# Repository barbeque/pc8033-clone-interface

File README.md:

# PC-8033 Clone Interface
This open-source hardware allows original-model NEC PC-8001 computers to use intelligent-type floppy drives such as the PC-8031-2W and PC-80S31.

## BOM
Please consult the [interactive bom](/bom/) for the most helpful view.

| Reference | Component | Digi-Key link | Comment |
|------|-----------|---------------|---------|
| C1 | 220µF capacitor | | |
| C2 | 0.1µF capacitor | | |
| R1 | 4.7kΩ resistor | | |
| U1 | 2x25-pin (50-pin) pin header | | |
| U2 | DIP 74LS32 | | |
| U3 | DIP 74LS04 | | |
| U4 | DIP Intel (or clone) 8255 | | |
| U5 | DIP 74LS30 | | |
| RN1, RN2, RN3 | 4.7kΩ bussed 8-resistor network (9-pin) | | |
| J2 | 2x17 (PC-8031) or 2x18 (PC-80S31) pin header | | |

## Cable from PC-8001
A 50-pin female edge connector and 50-pin female 0.1" IDC header are required. Crimp a straight 50-pin ribbon cable, such that pin 1 of the edge connector connects to pin 1 of the female IDC header. Attach to PC-8033 clone board, paying attention to board callout for pin "01."

## Cable to Floppy Drive
A cable will have to be made to connect to the disk drive.

### PC-8031-2W (34-pin edge connector)
Use an IDC crimper to crimp a 34-pin ribbon into 34-pin female (0.1") and 34-pin edge connector. Do not cross over (pin 1 on J2 should be pin 1 on the floppy drive.)

Connect to floppy drive, paying attention to pin 1 arrow on back.

### PC-80S31 (36-pin 57-series Centronics)
Use an IDC crimper to crimp a 36-pin ribbon into a 36-pin female (0.1") and 36-pin Centronics connector. Do not cross over.

Connect to floppy drive.

## Enclosure
TBD

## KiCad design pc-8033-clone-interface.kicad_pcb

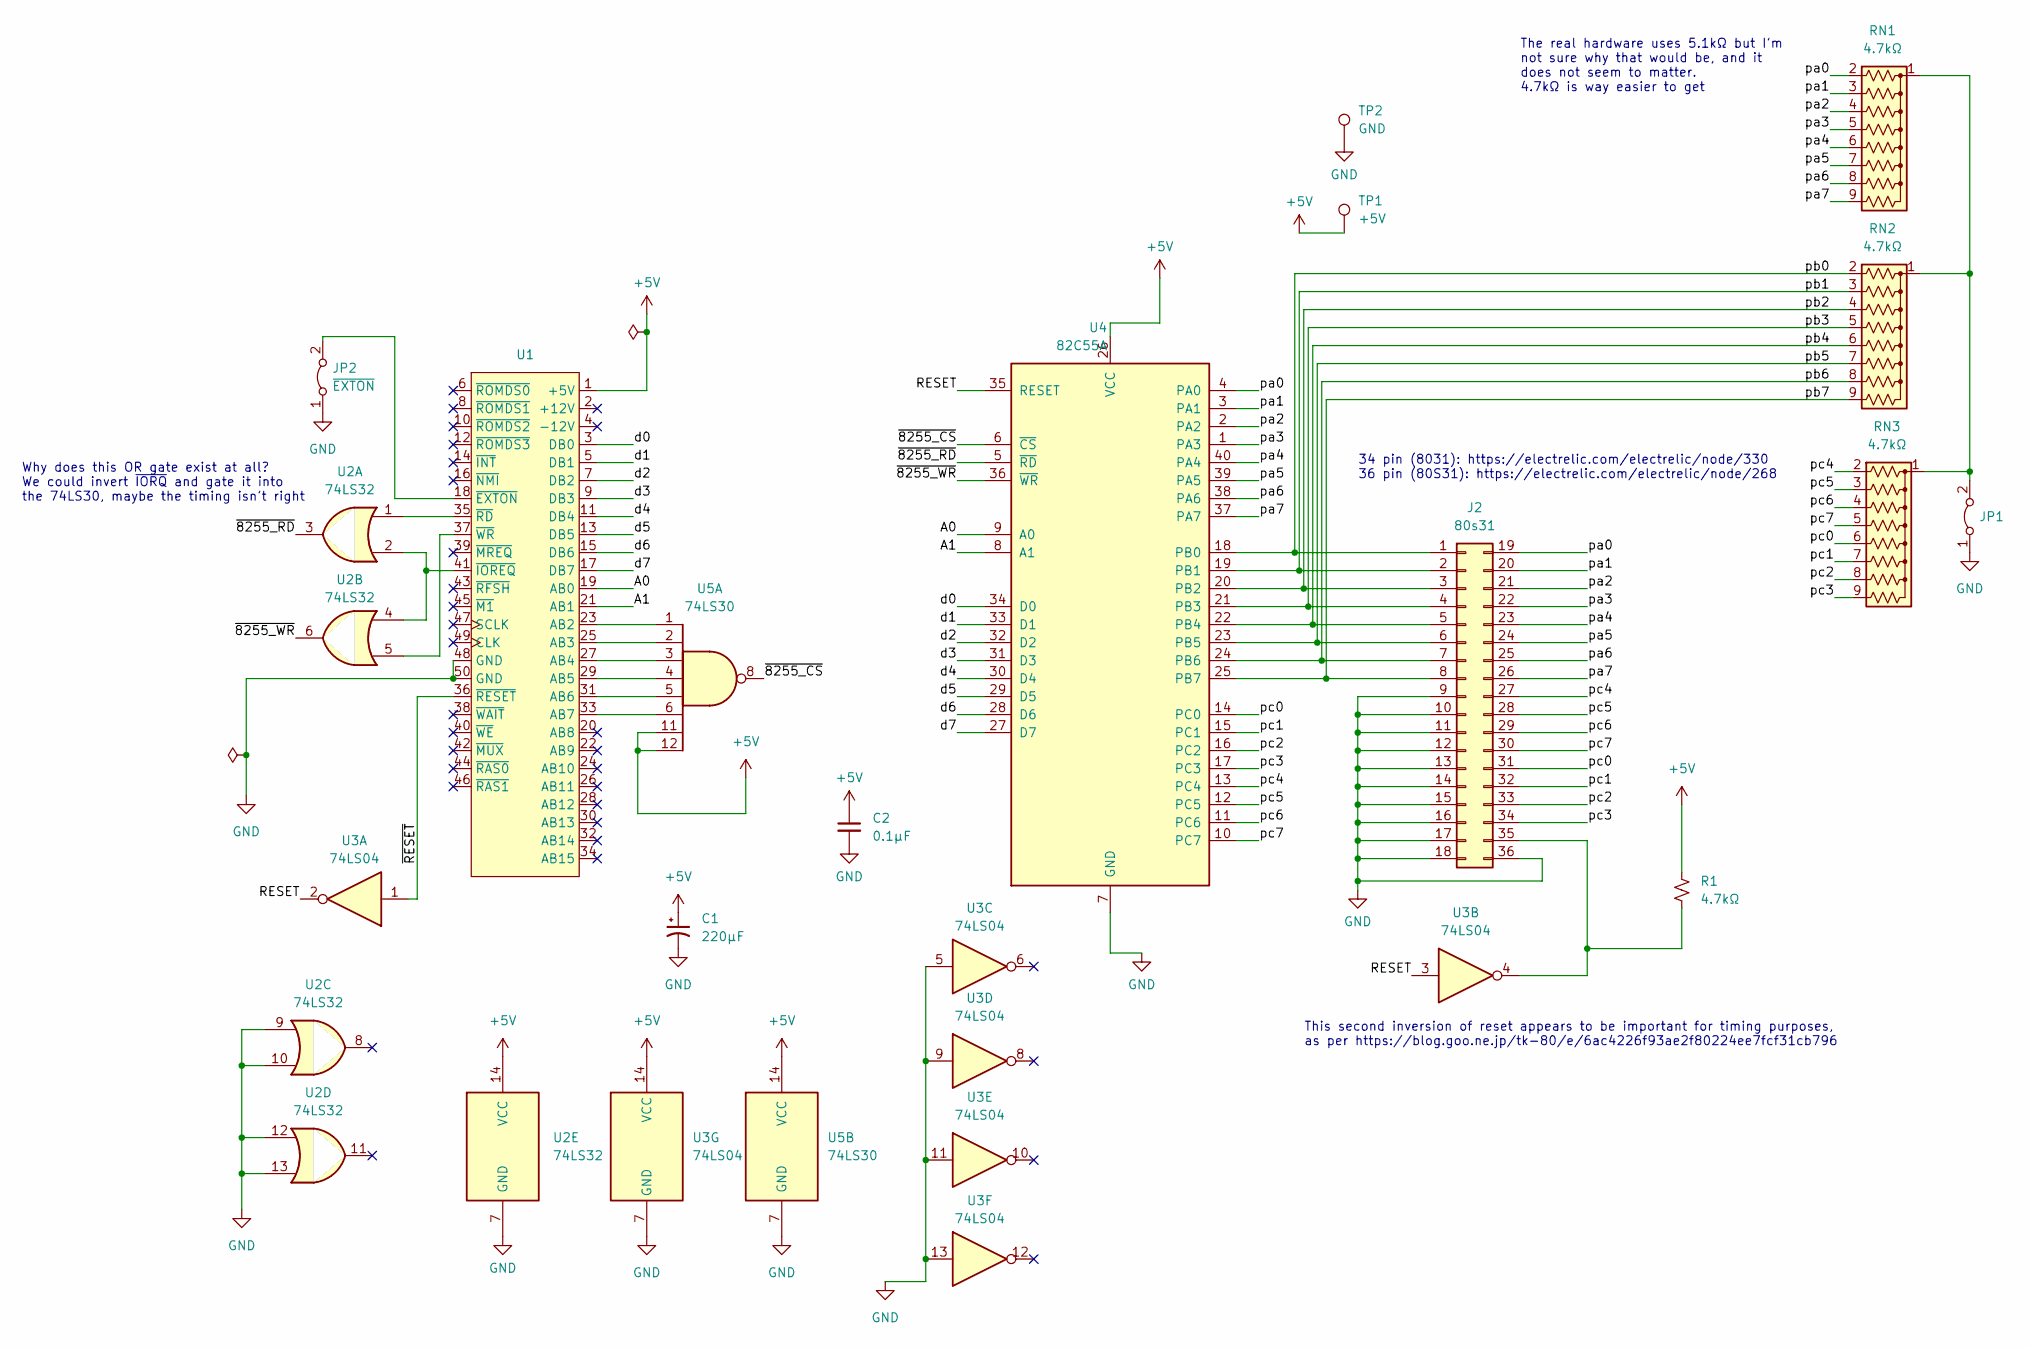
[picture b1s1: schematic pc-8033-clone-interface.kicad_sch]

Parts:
C1: 220µF; CP_Radial_D6.3mm_P2.50mm
C2: 0.1µF; C_Disc_D3.4mm_W2.1mm_P2.50mm
J2: 80s31; Centronics_36_FDD
JP1: Jumper_2_Bridged; SolderJumper-2_P1.3mm_Bridged2Bar_Pad1.0x1.5mm
JP2: ~{EXTON}; SolderJumper-2_P1.3mm_Bridged2Bar_Pad1.0x1.5mm
R1: 4.7kΩ; R_Axial_DIN0309_L9.0mm_D3.2mm_P12.70mm_Horizontal
RN1, RN2, RN3: 4.7kΩ; R_Array_SIP9
TP1: +5V; TestPoint_Loop_D1.80mm_Drill1.0mm_Beaded
TP2: GND; TestPoint_Loop_D1.80mm_Drill1.0mm_Beaded
U1: PinHeader_2x25_P2.54mm_Vertical
U2: 74LS32
U3: 74LS04
U4: 82C55A; DIP-40_W15.24mm
U5: 74LS30; DIP-14_W7.62mm_Socket_LongPads

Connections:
+5V: C1.1, C2.1, R1.1, TP1.1, U1.1 (+5V), U2.14 (VCC), U3.14 (VCC), U4.26 (VCC), U5.11, U5.12, U5.14 (VCC)
/A0: U1.19 (AB0), U4.9 (A0)
/A1: U1.21 (AB1), U4.8 (A1)
/RESET: U3.2, U3.3, U4.35 (RESET)
/d0: U1.3 (DB0), U4.34 (D0)
/d1: U1.5 (DB1), U4.33 (D1)
/d2: U1.7 (DB2), U4.32 (D2)
/d3: U1.9 (DB3), U4.31 (D3)
/d4: U1.11 (DB4), U4.30 (D4)
/d5: U1.13 (DB5), U4.29 (D5)
/d6: U1.15 (DB6), U4.28 (D6)
/d7: U1.17 (DB7), U4.27 (D7)
/pa0: J2.19, RN1.2 (R1), U4.4 (PA0)
/pa1: J2.20, RN1.3 (R2), U4.3 (PA1)
/pa2: J2.21, RN1.4 (R3), U4.2 (PA2)
/pa3: J2.22, RN1.5 (R4), U4.1 (PA3)
/pa4: J2.23, RN1.6 (R5), U4.40 (PA4)
/pa5: J2.24, RN1.7 (R6), U4.39 (PA5)
/pa6: J2.25, RN1.8 (R7), U4.38 (PA6)
/pa7: J2.26, RN1.9 (R8), U4.37 (PA7)
/pb0: J2.1, RN2.2 (R1), U4.18 (PB0)
/pb1: J2.2, RN2.3 (R2), U4.19 (PB1)
/pb2: J2.3, RN2.4 (R3), U4.20 (PB2)
/pb3: J2.4, RN2.5 (R4), U4.21 (PB3)
/pb4: J2.5, RN2.6 (R5), U4.22 (PB4)
/pb5: J2.6, RN2.7 (R6), U4.23 (PB5)
/pb6: J2.7, RN2.8 (R7), U4.24 (PB6)
/pb7: J2.8, RN2.9 (R8), U4.25 (PB7)
/pc0: J2.31, RN3.6 (R5), U4.14 (PC0)
/pc1: J2.32, RN3.7 (R6), U4.15 (PC1)
/pc2: J2.33, RN3.8 (R7), U4.16 (PC2)
/pc3: J2.34, RN3.9 (R8), U4.17 (PC3)
/pc4: J2.27, RN3.2 (R1), U4.13 (PC4)
/pc5: J2.28, RN3.3 (R2), U4.12 (PC5)
/pc6: J2.29, RN3.4 (R3), U4.11 (PC6)
/pc7: J2.30, RN3.5 (R4), U4.10 (PC7)
/~8255_CS: U4.6 (~CS), U5.8
/~8255_RD: U2.3, U4.5 (~RD)
/~8255_WR: U2.6, U4.36 (~WR)
/~RESET: U1.36 (~RESET), U3.1
GND: C1.2, C2.2, J2.9, J2.10, J2.11, J2.12, J2.13, J2.14, J2.15, J2.16, J2.17, J2.18, J2.36, JP1.1 (A), JP2.1 (A), TP2.1, U1.48 (GND), U1.50 (GND), U2.7 (GND), U2.9, U2.10, U2.12, U2.13, U3.5, U3.7 (GND), U3.9, U3.11, U3.13, U4.7 (GND), U5.7 (GND)
unnamed: J2.35, R1.2, U3.4
unnamed: JP1.2 (B), RN1.1 (common), RN2.1 (common), RN3.1 (common)
unnamed: JP2.2 (B), U1.18 (~EXTON)
unnamed: U1.23 (AB2), U5.1
unnamed: U1.25 (AB3), U5.2
unnamed: U1.27 (AB4), U5.3
unnamed: U1.29 (AB5), U5.4
unnamed: U1.31 (AB6), U5.5
unnamed: U1.33 (AB7), U5.6
unnamed: U1.41 (~IOREQ), U2.2, U2.4
unnamed: U1.35 (~RD), U2.1
unnamed: U1.37 (~WR), U2.5

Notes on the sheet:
The real hardware uses 5.1kΩ but I'm not sure why that would be, and it does not seem to matter. 4.7kΩ is way easier to get
This second inversion of reset appears to be important for timing purposes, as per https://blog.goo.ne.jp/tk-80/e/6ac4226f93ae2f80224ee7fcf31cb796
Why does this OR gate exist at all? We could invert ~{IORQ} and gate it into the 74LS30, maybe the timing isn't right
34 pin (8031): https://electrelic.com/electrelic/node/330 36 pin (80S31): https://electrelic.com/electrelic/node/268

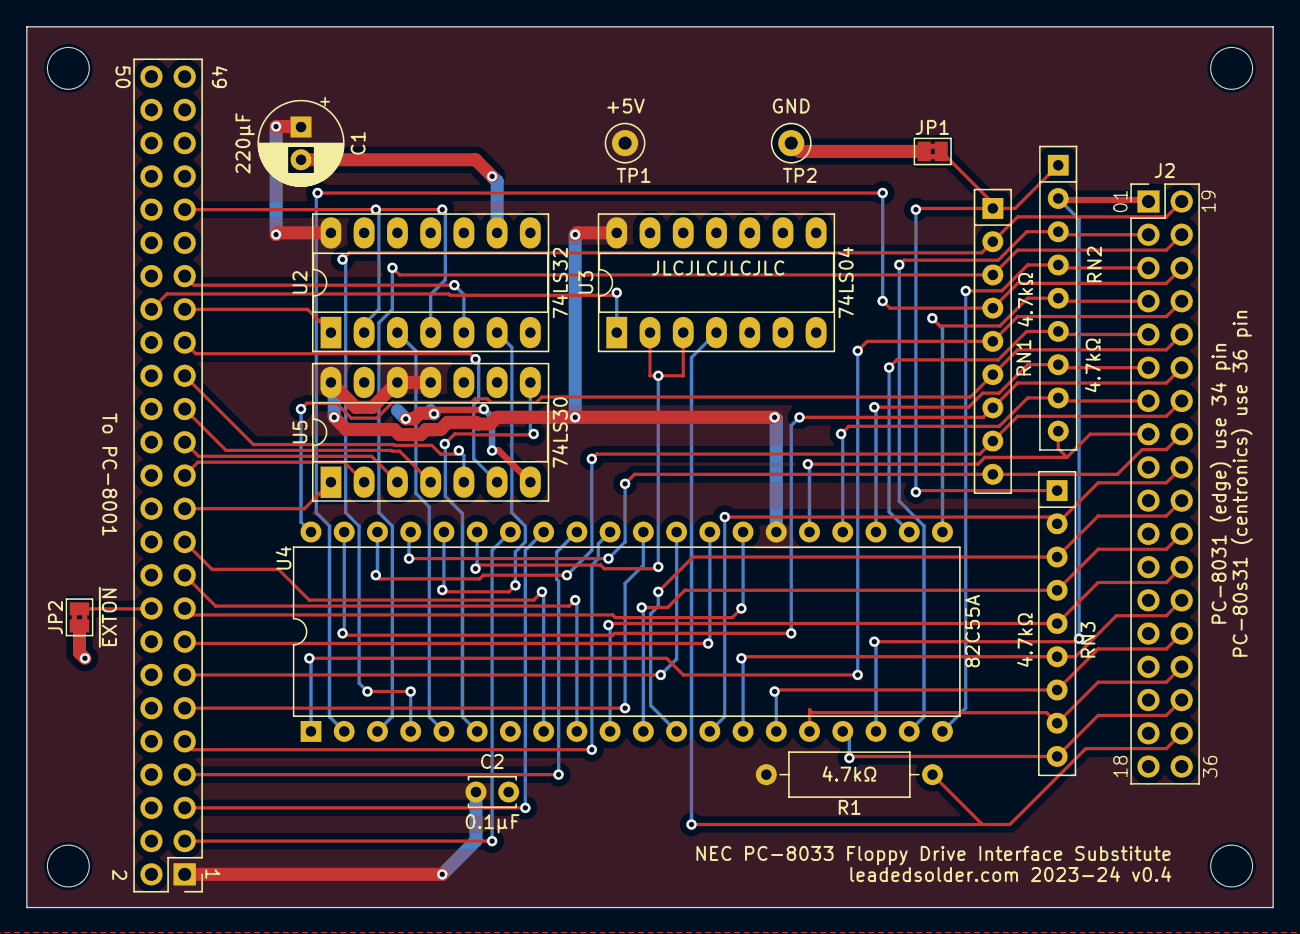
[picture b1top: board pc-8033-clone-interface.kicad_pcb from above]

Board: 2 copper layers, 95.2 x 67.3 mm, 16 parts (0 on the bottom side), 53 nets.

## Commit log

2023-10-05 Initial wire up from 8001 to 8255
2023-10-05 Still trying to puzzle out the interface here
2023-10-05 Now we're getting into the troubles
2023-10-05 Reset faffing
2023-10-05 EXTON strapped low
2023-10-05 Pull-downs
2023-10-06 Capture dual footprint IDC header
2023-10-06 Clean up stale TODO
2023-10-06 Clean up schem warnings
2023-10-06 Lots of clearance issues...
2023-10-06 Tear drops
2023-11-27 V1 released to fab
2023-12-29 Rotate 50-pin connector
2024-02-19 Short the EXTON pin instead of trying to gently pull it down
2024-02-19 add a smaller decoupling cap on the 8255
2024-02-19 Use weird Centronics pinout on board
2024-02-19 V2 sent to JLCPCB
2024-03-01 V3: fix the pinout once and for all
2024-03-17 Fix select logic
2024-03-25 Add header pin numbers to the underside for kicks
2024-03-26 Move a pullup to look nicer
2024-06-10 Some self-doubt comments
2024-06-10 To-do list
2024-06-11 ibom
2024-06-11 Case
2024-06-11 Case with deeper lid
2024-06-11 logo on top
